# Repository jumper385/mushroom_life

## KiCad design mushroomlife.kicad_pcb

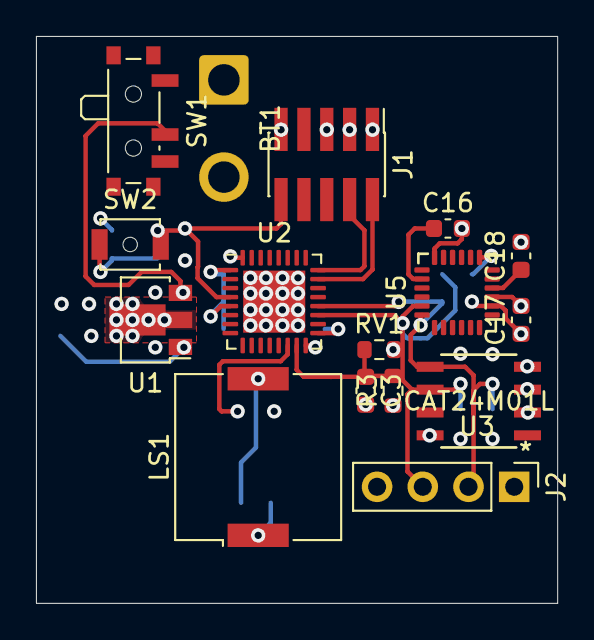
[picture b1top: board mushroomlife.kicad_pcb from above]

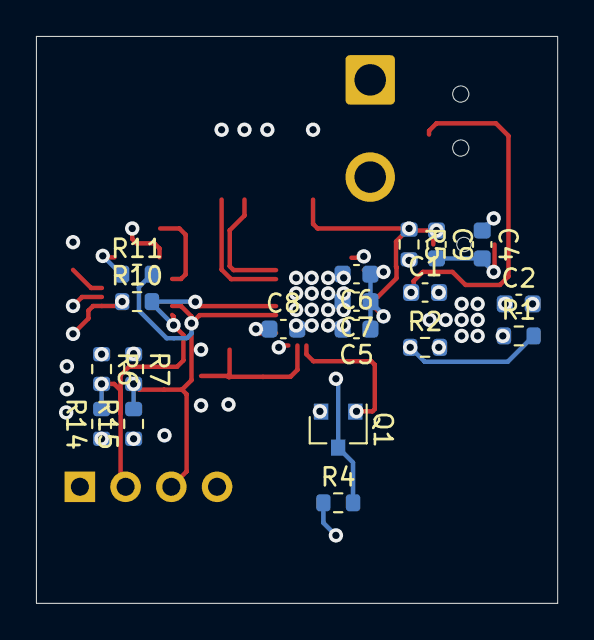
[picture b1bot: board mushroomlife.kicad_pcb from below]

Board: 4 copper layers, 29.0 x 31.5 mm, 35 parts (19 on the bottom side), 15 nets.

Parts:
BT1: Battery; SolderWire-1sqmm_1x02_P5.4mm_D1.4mm_OD2.7mm
C1, C2: 10uF; C_0603_1608Metric
C3, C7: 1uF; C_0603_1608Metric
C4: 4.7uF; C_0603_1608Metric
C5: 10nF; C_0603_1608Metric
C6, C8, C9, C17, C18: 0.1uF; C_0603_1608Metric
C16: 2.2nF; C_0603_1608Metric
J1: Conn_ARM_JTAG_SWD_10; PinHeader_2x05_P1.27mm_Vertical_SMD
J2: Conn_01x04_Male; PinHeader_1x04_P2.54mm_Vertical
LS1: Speaker_Crystal; Buzzer_Murata_PKMCS0909E4000-R1
Q1: BSS138; SOT-23
R1, R2: R; R_0603_1608Metric
R3, R5, R6, R7, R10, R11, R14, R15: 10k; R_0603_1608Metric
R4: 1k; R_0603_1608Metric
RV1: Varistor; R_0603_1608Metric
SW1: SW_SPST; SW_SPDT_PCM12
SW2: SW_SPST; SW_SPST_B3U-1000P-B
U1: LM317L_SOT-89; SOT-89-3
U2: STM32L432KBUx; QFN-32-1EP_5x5mm_P0.5mm_EP3.45x3.45mm
U3: CAT24M01L; CAT24M01WI-GT3
U5: MPU-6050; InvenSense_QFN-24_4x4mm_P0.5mm

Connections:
/Accelerometer + Pedometer/I2C_SCL: J2.3, R7.2, R11.2, R15.2, U2.19, U3.6, U5.23
/Accelerometer + Pedometer/I2C_SDA: J2.2, R6.2, R10.2, R14.2, U2.20, U3.5, U5.24
/MCU/LIGHT_IN: C3.1, R3.2, RV1.1, U2.15
/MCU/NRST: C9.1, J1.10, R5.1, SW2.2, U2.4
/MCU/SPEAKER: Q1.1, U2.14
/SWCLK: J1.4, U2.24
/SWDIO: J1.2, U2.23
GND: BT1.2, C1.2, C2.2, C3.2, C4.2, C5.2, C6.2, C7.2, C8.2, C9.2, C16.2, C17.2, C18.2, J1.3, J1.5, J1.9, J2.4, Q1.2, R2.2, RV1.2, SW2.1, U2.16, U2.32, U2.33, U3.3, U3.4, U5.9, U5.18
unnamed: C1.1, SW1.2, U1.3
unnamed: C16.1, U5.20
unnamed: C18.1, U5.10
unnamed: LS1.2, Q1.3, R4.2
unnamed: R1.2, R2.1, U1.1
VCC: BT1.1, SW1.1
VDD: C2.1, C4.1, C5.1, C6.1, C7.1, C8.1, C17.1, J1.1, J2.1, LS1.1, R1.1, R3.1, R4.1, R5.2, R6.1, R7.1, R10.1, R11.1, R14.1, R15.1, U1.2, U2.1, U2.5, U2.17, U3.2, U3.8, U5.8, U5.13

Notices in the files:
parts and their libraries:
Copyright 2016 Accelerated Designs. All rights reserved.
